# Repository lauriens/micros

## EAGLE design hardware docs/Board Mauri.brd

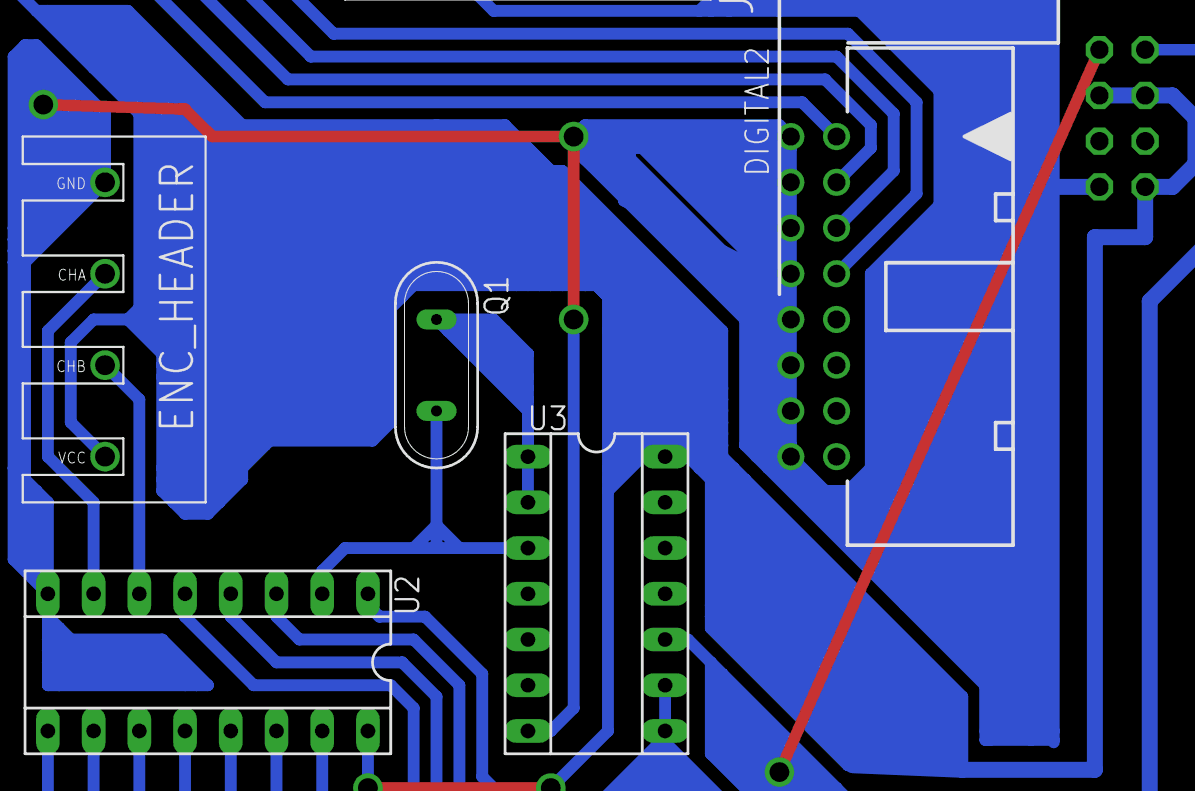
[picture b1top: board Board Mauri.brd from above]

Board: 2 copper layers, 5 parts (1 on the bottom side), 7 nets.

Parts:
DIGITAL2: PAK100/2500-5-16
MOTOR_HEADER: MA04-2
Q1: QS
U2: SOCKET-16
U3: SOCKET-14

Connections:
S$2: Q1.1, U3.1, U3.2
S$4: U2.8, U3.7
S$7: MOTOR_HEADER.3, MOTOR_HEADER.4, MOTOR_HEADER.7, U2.16, U3.14
S$12: MOTOR_HEADER.2, U3.10
S$15: MOTOR_HEADER.1, U3.8, U3.9
S$24: Q1.2, U2.2, U3.3
S$40: DIGITAL2.1, DIGITAL2.3, DIGITAL2.5, DIGITAL2.7, DIGITAL2.9, DIGITAL2.11, DIGITAL2.13, DIGITAL2.15, MOTOR_HEADER.8

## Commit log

2018-09-18 Trabalho Final v1
2019-04-27 Atualizando repositório com a última versão do trabalho
2019-04-28 Software documentation updated; added documentation for the libQuanser (libv1) and for the pid
2019-05-04 ChangeHardwareDirectories
2019-06-19 Added Script.c, to generate the start script (IT DOESN'T WORK YET)
2019-06-26 Finished gpios from ios 0, 1 and 2
2019-06-27 Work especification (rules)
2019-07-03 it's not working on my computer, I'm hopeful it could work on the lab's pcs? cause I used functions I had already tested and they perviously worked, but now don't and idk what's happening
